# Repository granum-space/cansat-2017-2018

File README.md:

# cansat-2018
Проект команды Granum чемпионата Cansat в России 2017-2018 года

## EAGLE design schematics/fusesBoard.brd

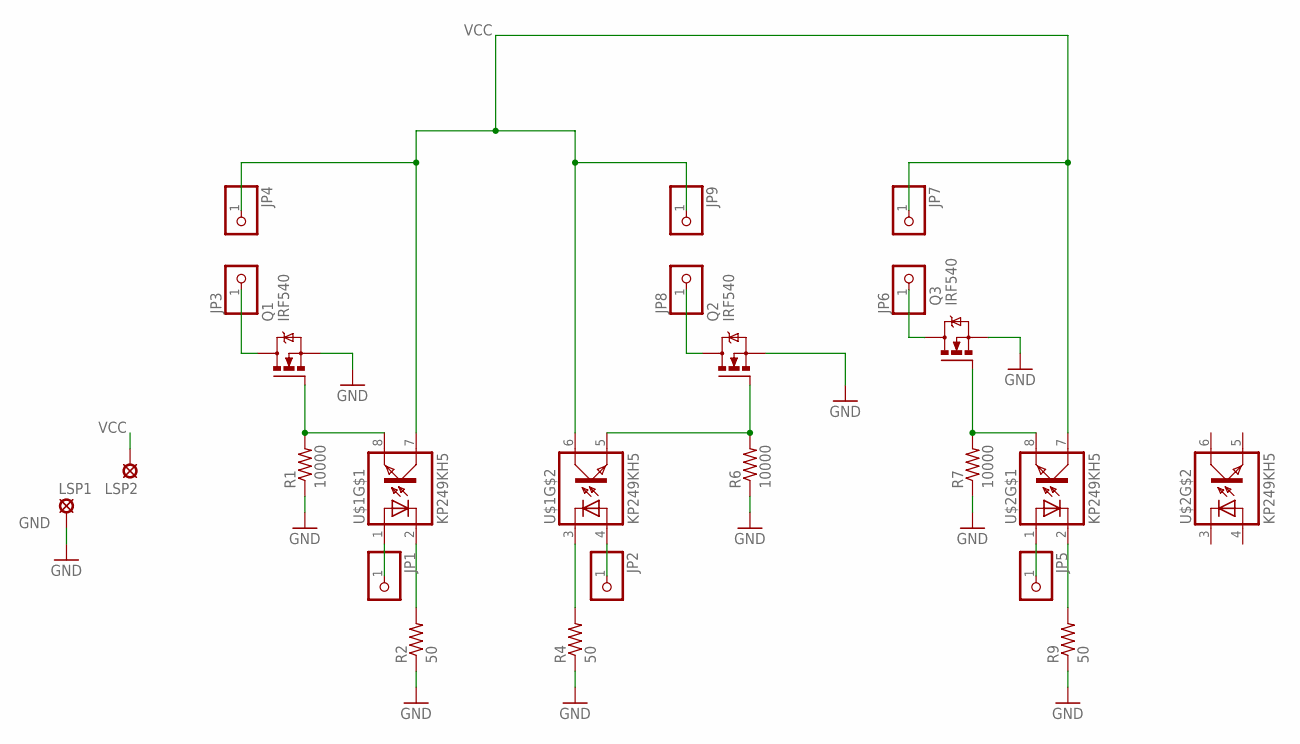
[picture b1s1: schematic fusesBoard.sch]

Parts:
JP1, JP2, JP3, JP4, JP5, JP6, JP7, JP8, JP9: PINHD-1X1; 1X01
LSP1, LSP2: SE14
Q1, Q2, Q3: IRF540; TO220BV
R1, R6, R7: 10000; 0204/7
R2, R4, R9: 50; 0204/7
U$1, U$2: KP249KH5; DIL08

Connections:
CTRL1: JP1.1, U$1.1
CTRL2: JP2.1, U$1.4
CTRL3: JP5.1, U$2.1
GATE1: Q1.G, R1.2, U$1.8
GATE2: Q2.G, R6.2, U$1.5
GATE3: Q3.G, R7.2, U$2.8
GND: LSP1.MP, Q1.S, Q2.S, Q3.S, R1.1, R2.1, R4.1, R6.1, R7.1, R9.1
unnamed: R2.2, U$1.2
unnamed: R9.2, U$2.2
unnamed: R4.2, U$1.3
SOURCE1: JP3.1, Q1.D
SOURCE2: JP8.1, Q2.D
SOURCE3: JP6.1, Q3.D
VCC: JP4.1, JP7.1, JP9.1, LSP2.MP, U$1.6, U$1.7, U$2.7

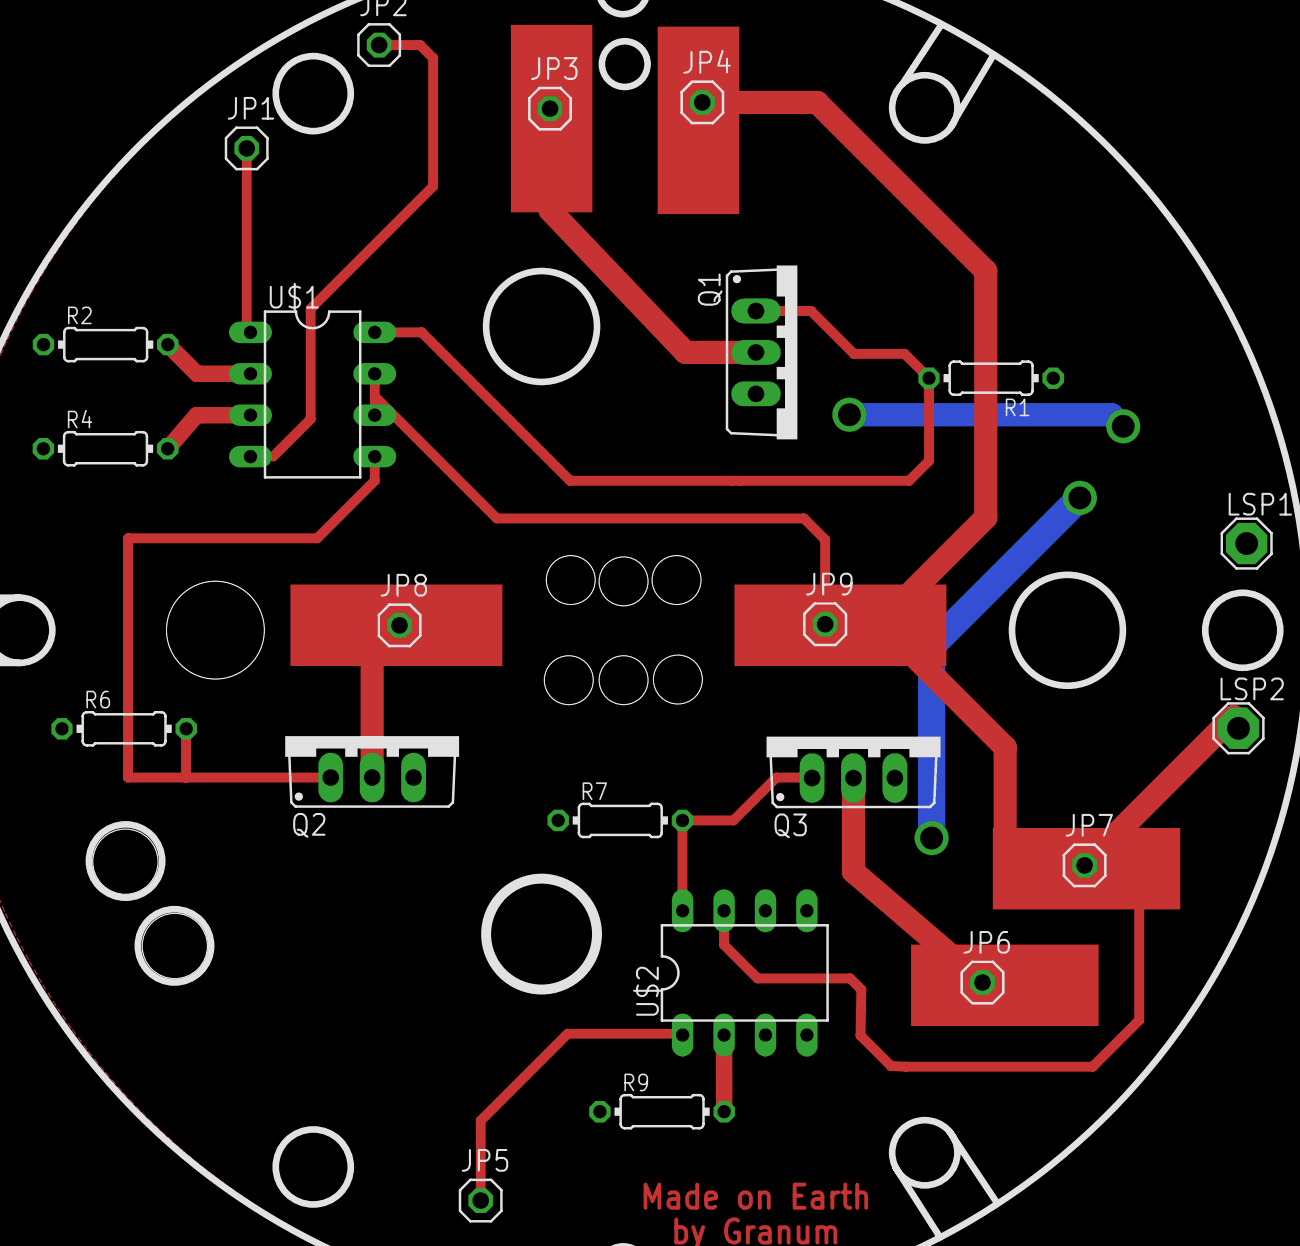
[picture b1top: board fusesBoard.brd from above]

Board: 2 copper layers, 22 parts (0 on the bottom side), 14 nets.

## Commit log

2017-10-31 Создана структура каталогов и загружены модели архимедового винта
2017-10-31 забытые детали архимедового винта и спектрометр
2017-11-06 Добавлен тест фильтра Маджвика
2017-11-16 частично готовый, полностью переработанный спектрометр
2017-11-16 чертеж для щели
2017-11-20 Перенес конструкцию в отдельный каталог
2017-11-20 Добавил черновую версию сервера для спектрометра
2017-11-23 Сервер упрощен и проверен
2017-11-23 Клиент показывает картинку!
2017-11-23 Добавил структурную схему
2017-11-24 Относительно приемлимо работает. Об измерении спектра речи пока не идет
2017-11-28 Код волосатый, но завтра можно будет работать
2017-11-28 Добавил возможность "заморозки" графика для сравнений
2017-11-28 Косяк с компиляцией (Несколько непонятный, нужно будет разобраться)
2017-12-23 Добавлен экспорт графика в файл, починены перепутанные цвета
2017-12-23 Добвалены (не доделаны) слайдеры настроек
2017-12-24 Реализовано растяжение гистограммы яркости, улучшены слайдеры
2017-12-27 Add files via upload
    Помимо основной схемы добавлено разделение бортового комплекса управления(БКУ), а именно:
    /* внимание: дальше будет много аббревиатур */
    СЭП - система электропитания
    СУДН - система управления движением и навигацией
    СУБА - система управления бортовой аппаратурой
    БРК - бортовой радио комплекс
2017-12-30 наброски контейнера для парашюта
2017-12-30 в архитектуре подправлены недочеты
    и добавлены фотографии компонентов
2017-12-30 а вот и фотографии
2017-12-30 Начата "Нежность", добавлена схема ПО
2018-01-05 Проект для теста работы с омнибасом. Настроен на работу с FPU и прочим. Очень сырой и корявый
2018-01-07 Нежность, старые модели, изменения в архитектуре
2018-01-10 Навел порядок с картинками
2018-01-10 Схемы
2018-01-13 Нафоткано
2018-01-16 спектрометр на слайды
2018-01-16 поправил схему БРКэ
2018-01-17 Added chute
2018-01-17 Фотографии возвращены в отделную папку
2018-01-17 В этом файле ПО переделано под презентацию
2018-01-17 Последние изменения
2018-01-18 Переведена схема ПО для ПЗ, пофикшена тень текста в ПО для презентации
2018-01-20 Исправил схему БКУ
2018-01-21 Добавил общие модели
2018-01-21 Убрал старые версии
2018-01-21 Намоделено немного электроники, сделал для неё папочку, переместил туда батарейку
2018-01-21 Омнибас доработан по натурной модели
2018-01-21 Добавил модель сонара
2018-01-21 Исправил оптическую схему под новые веяния
2018-01-22 Auto stash before merge of "master" and "origin/master"
    Правим схемы
2018-01-22 Линзы для ПЗ
2018-01-22 Продолжаем править схемы
2018-01-22 Черновая модель системы "Зацепка"
2018-01-23 Затравка для отсека для парашюта
2018-01-24 пофикшен БКУ
2018-01-25 Картиночки да схемочки, схемочки да картиночки!
2018-01-27 Конструкция готова!(почти)
2018-01-27 ПЗ, которая ушла на печать
2018-01-27 компановка
2018-01-27 удаленные
2018-01-28 Разбил схемы спектрометра на две. Вроде как навел порядок в структуре?
2018-01-28 Сборки с поддержками для печати частей спектрометра
2018-02-10 Начата работа над единой абстракцией для единообразного доступа к внешним устройствам
2018-02-17 Вырисовывается чёткая структура devctl
2018-02-21 Devctl почи закончен (осталось протестировать и добавить работу с потоковыми интерфейсами)
2018-02-21 новый отсек системы спасения на печать.
2018-03-03 Многое поправлено, начата тестовая интеграция с драйвером BMP
2018-03-10 конструкция
2018-03-10 Реструктуризация каталогов
2018-03-10 Добавил nuttx
2018-03-10 Добавил apps из чистого nuttx 7.24 https://bitbucket.org/nuttx/apps/commits/0b3ce51a0ed61da3048d8611a70d7280132ae513
2018-03-10 добавил папочку с "нашими" приложениями
2018-03-11 Удалил старые каталоги и начал добавлять поддержку мавлинка
2018-03-11 Добавил наш форк мавлинка
2018-03-11 Мейкфайл для генерации мавлинковски сообщений
2018-03-11 Добавил тестовое кастомное сообщение и пару тестовых програмок на питоне и на си
2018-03-16 моя версия драйвера
2018-03-17 последняя версия конструкции с передаланными платформой, отсеком СС, все еще с зеркалами
2018-03-17 к ОСС добавлен текстолит с двумя пережигалками, осталось только сделать пережигалку на зацепку и можно на печать
2018-03-17 Навел порядок с версионированием моделей (и сделать скрипт для этого)
2018-03-18 Перемоделил нижный отсек
2018-03-18 Дырки для доставания батарейки
2018-03-23 Добавил шаблон проекта для stm8 на sdcc из https://community.st.com/docs/DOC-1963-my-project
2018-03-23 Добавил проект для сервы (с эклипсом), удалил лишнее
2018-03-24 плата для пережигателей расчерчена под особенности аппарата
2018-03-24 привели в порядок nuttx репозиторий повторный коммит сонара
2018-03-25 готова схема платы с пережигателями
2018-03-25 Работы над тестом NRF
2018-03-25 код для сервы
2018-03-26 NRF доведён до рабочего состояния
2018-03-27 разведена плата для пережигателей
2018-03-28 продолжение работы с сонаром. консоль заработала, а драйвер почти заработал
2018-03-30 Закончен тест НРФа
2018-03-31 сонар доведен до рабочего состояния, warnings устранены.
2018-03-31 обновился nuttx
2018-04-11 сделаны площадки под пережигатели, увеличена ширина дорожек
2018-04-14 код для сервы на i2c
2018-04-17 Затравки наземки
2018-04-18 К черту sql, будет redis
2018-04-19 Потому что редис - это круто
2018-04-20 Затравочка для приёмной станции
2018-04-21 Тесты мпу и минмеа
2018-04-21 переразведенная схема платы
2018-04-21 последняя версия модели перед печатью для видео
2018-04-22 made on earth
2018-04-22 Поддержки для окошка для пережигателя и ремонт самого окошка
2018-04-22 Сделал графики для ускорения и дуса. немножечко отстилизовал
2018-04-22 Особенности перезда на сервер
2018-04-23 Тестовый эмиттер теперь может давать "телеметрию" не только на локалхост Мавлинковское приложение слушает не только локалхост
2018-04-23 Добавил юниты для systemd
2018-04-23 Попытка починить логи, чтобы systemd не смывало потоком
2018-04-23 модель после поломки
2018-04-25 Пробы графиков
2018-04-25 Борт отправляет данные IMU
2018-04-25 Переделки, чтобы каждый раз отдавать только новые записи и переход на свои сообщения для MPU6000
2018-04-27 Добавил считалку углов дифрешетки
2018-04-27 Наземка переделана, чтобы отсылать клиенту только новые записи
2018-04-29 Теперь можно компилить и на донную нанопи
2018-04-29 Доделан BMP, начата карта
2018-04-30 Линии, рисующиеся из редиса и поповеры по ним
2018-04-30 С борта отправляются пакеты gps
2018-05-01 Починил графики, доделал карту
2018-05-01 Начата интеграция сонара
2018-05-01 Затравочка под webgl
2018-05-02 Сонар добит
2018-05-02 Ракета интегрирована в плотсы
2018-05-04 Попытка Маджвика (не пытка)
2018-05-12 Ещё одна неудачная пытка в маджвика
2018-05-18 Доделан Маджвик
2018-05-18 Продолжаем работу над датчиком освещенности
2018-05-18 Работающий пример датчика влажности и температуры
2018-05-18 Исправлены опечатки и забывайки
2018-05-18 Добавил конфигурацию, в которой проект наиболее близок к тому, чтобы собираться
2018-05-19 Датчик освещенности работает! Представляете?
2018-05-20 Первая степень готовности к испытаниям
2018-05-21 Телеметрия с тестового пуска и скрипты для её обработки и проигрывания
2018-05-22 Телеметрия с сегодняшнего полета
2018-05-26 Состояние на момент 2 и 3 запуска
2018-05-26 Дописан и оттестирован драйвер lsm303c
2018-05-26 Начата "лепка" финального кода
2018-05-27 другой вариант спектрометра
2018-05-29 предварительный вариант отсека сс
2018-05-29 Перенесено окошко для бокового пережигателя и сделаны отверстия для проводов
2018-05-31 Расписаны все треды, осталось тестирование, разбор пакетов от малинки и главный поток управления
2018-06-02 Начат перенос программы для спектров на rpi
2018-06-02 доработки по аппарату
2018-06-02 Попытки переехать на modwsgi
2018-06-03 Попытка переосмысления тела спектрометра
2018-06-04 Теперь в миллиметрах
2018-06-04 Обновление ресурсов переведено на таймауты, моделька кансата вместо ракеты
2018-06-10 Бортовой код доведён до запуска
2018-06-12 теперь все запускается под gunicorn
2018-06-13 Пофикшен баг с ОВЕРЧЕРЕЗМЕРНЫМ потреблением CPU из-за модельки, тест динамического обновления картинок
2018-06-13 Улучшено оформление
2018-06-14 добавлен файл для получения и сохранения
    телеметрии со спектрами и картинкой
2018-06-15 переписала датчик влажности и температуры на python
2018-06-16 добавлен модуль для взаимодействия с am2320
    передача и прием телеметрии по мавлинку (еще не тестила)
2018-06-17 Перенос датчика влажности в отдельную папку
2018-06-17 не закоммиченные ранее мавлинсковские сообщения для данных от камеры спектрометра и датчика влажности, температуры
2018-06-17 работает передача и прием данных от am2320 по мавлинку
2018-06-17 в сообщениях изменен тип для времени из-за возникающего переполнения
2018-06-17 Текущие изменения кода
2018-06-17 Эксперименты со звуком
2018-06-20 Наработки по звуку
2018-06-21 Сделан стриминг звука (на /sound)
2018-06-21 Добавлен скомпиленный на бортовой малинке драйвер i2s
2018-06-22 расшифровка мавлинковских сообщений и сохранение данных в csv сообщения со спектрами сохраняются по-своему, чтобы легче строить графики в granum.xml добавила поле для положения сервы
2018-06-22 файлы для обработки данных уже после полета: программа для подсчета интенсивностей со снимка спектра и программа для построения трехмерной поверхности по мавлинковским сообщениям, связанным со спектр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
2018-06-22 Акцепторы спектров вынесены в отдельные классы
2018-06-22 Сделан вывод спектров на сайт
2018-06-23 откалибровали спектрометр, теперь графики строим от нанометров, а не от строчек. добавила более точную функцию перевода нанометров в RGB, чтобы график был более наглядным
2018-06-24 добавила поле, обозначающее координату по Y обрезки снимка спектра
2018-06-24 Текущие изменения
2018-06-24 добавила работающие сервисы для спектрометрии и датчика влажности/температуры на raspberry pi
2018-06-24 Добавлены сервисы с pharos
2018-06-24 поправила максимумы для графиков, добавила комментарии; оставшееся с калибровки: csv-файлы с графиками лазеров, программа для подсчета нанометров в зависимости от строчки картинки
2018-06-24 добавила декодировку и сохранение картинок по логам от мавлинка
2018-06-25 Исправлены ошибке в модуле звука
2018-06-25 Исправлены проблемы с висящими сокетами
2018-06-27 построение графиков по картинкам из логов мавлинка
2018-06-27 NRF работает LSM не работает
2018-06-27 Обобщенный проект для работы над прошивкой
2018-06-28 Заигнорил лишнее
2018-06-28 В конструкциях сделана FSM
2018-06-29 в тысячный раз переделанная конструкция аппарата, но нутром чую, что окончательная. Ура, товарищи!
2018-06-29 построение графиков спектра отражения
2018-06-29 юнит для автоматической настройки камеры при включении raspberry pi
2018-06-29 Оформлен модуль звука
2018-06-29 добавлен юнит для звукового модуля на raspberry pi. в связи с перемещением всех модулей в /opt также подправлены остальные юниты
2018-06-30 Текущие изменения в сообщениях
2018-07-01 Поддержка службы дефрагментирующей пакеты
2018-07-01 исправление ошибок в отображении 3д модели
2018-07-02 Много изменений
2018-07-02 Текущие фиксы
2018-07-02 Добавлены все графики, подправлена разметка
2018-07-02 Рефакторинг блюпринтов
2018-07-03 Изменения
2018-07-03 Готовность к предстаротовым
2018-07-03 Добавлено онлайн отображение статуса аппарата
2018-07-03 Изменены параметры логгирования дефрагментатора (Василий)
2018-07-03 Правки к графикам
2018-07-03 Состояние перед проверкой аппарата
2018-07-04 логи для фароса
2018-07-04 программа для работы с сервой на raspberry pi
2018-07-04 логи везде 5~везде
2018-07-04 телеметрия с наземной станции
2018-07-05 Результаты
2018-07-05 Обработка результатов полета
2018-07-05 Из видео удалено лишнее и добавлен список зависимостей для плоттера ориентации
2018-07-07 презентация с летней сессии
2018-07-09 С подготовки презентации
2018-07-10 Последние изменения перед запуском
2019-01-11 презентации с зимней сессии (чтобы не потерялись)
